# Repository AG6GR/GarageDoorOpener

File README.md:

# Garage Door Opener

<center></center>

A bare-bones ESP32 based HomeKit enabled garage door opener using [HomeSpan](https://github.com/HomeSpan/HomeSpan).

# Hardware

To avoid any modification to the garage door opener itself, I designed the board to use its own position sensor and emulate a wall switch to trigger the garage door movement. Some commercial products emulate a wireless remote and indeed the ESP32 does have some [special function hardware](https://github.com/HomeSpan/HomeSpan/blob/master/docs/RMT.md) for generating pulse code signals, however I decided to skip the complexity for this first revision as the holiday season presented some serious schedule pressure for getting this finished. Likewise, for the door position sensor some products use a tilt sensor with the assumption the board would be glued to the moving door itself. I again opted for the simpler solution of a microswitch mounted on one of the door's guide rails to avoid the complexity of dealing with battery power and wireless control.

<center></center>

To actuate the door, a wall switch normally would short a pair of lines connected to terminals on the back of the garage door opener. I measured these terminals with a voltmeter and found the high side was pulled up to 24V nominal, above some floating ground potential. Also of note is that the threshold voltage for triggering was quite low, less than 0.1V difference. The ideal part to use in this case would be a small relay, but I didn't have any on hand. As an alternative, I ended up using an optoisolator with an NPN transistor in a Darlington configuration to achieve the isolation and current capacity needed to drive the opener's trigger line low.

One unexpected issue that came up after the board arrived was that the NPN BJT was not fully turning on before the line voltage collapsed, leaving the line stuck at a ~0.7V base emitter diode voltage, which was just a bit above the threshold voltage for triggering the opener. I bodged in a 0.1 µF capacitor between the high/low side of the screw terminal to fix this. The extra capacitance ensures the BJT has just enough time to fully turn on, driving the line completely low and triggering the opener.

# Firmware

The firmware relies on the excellent [HomeSpan](https://github.com/HomeSpan/HomeSpan) project to implement HomeKit support. It was very straightforward to implement a GarageDoorOpener service and hook it up to the appropriate inputs/outputs. With some fine tuning of switch debouncing, everything was installed and ready by Christmas.

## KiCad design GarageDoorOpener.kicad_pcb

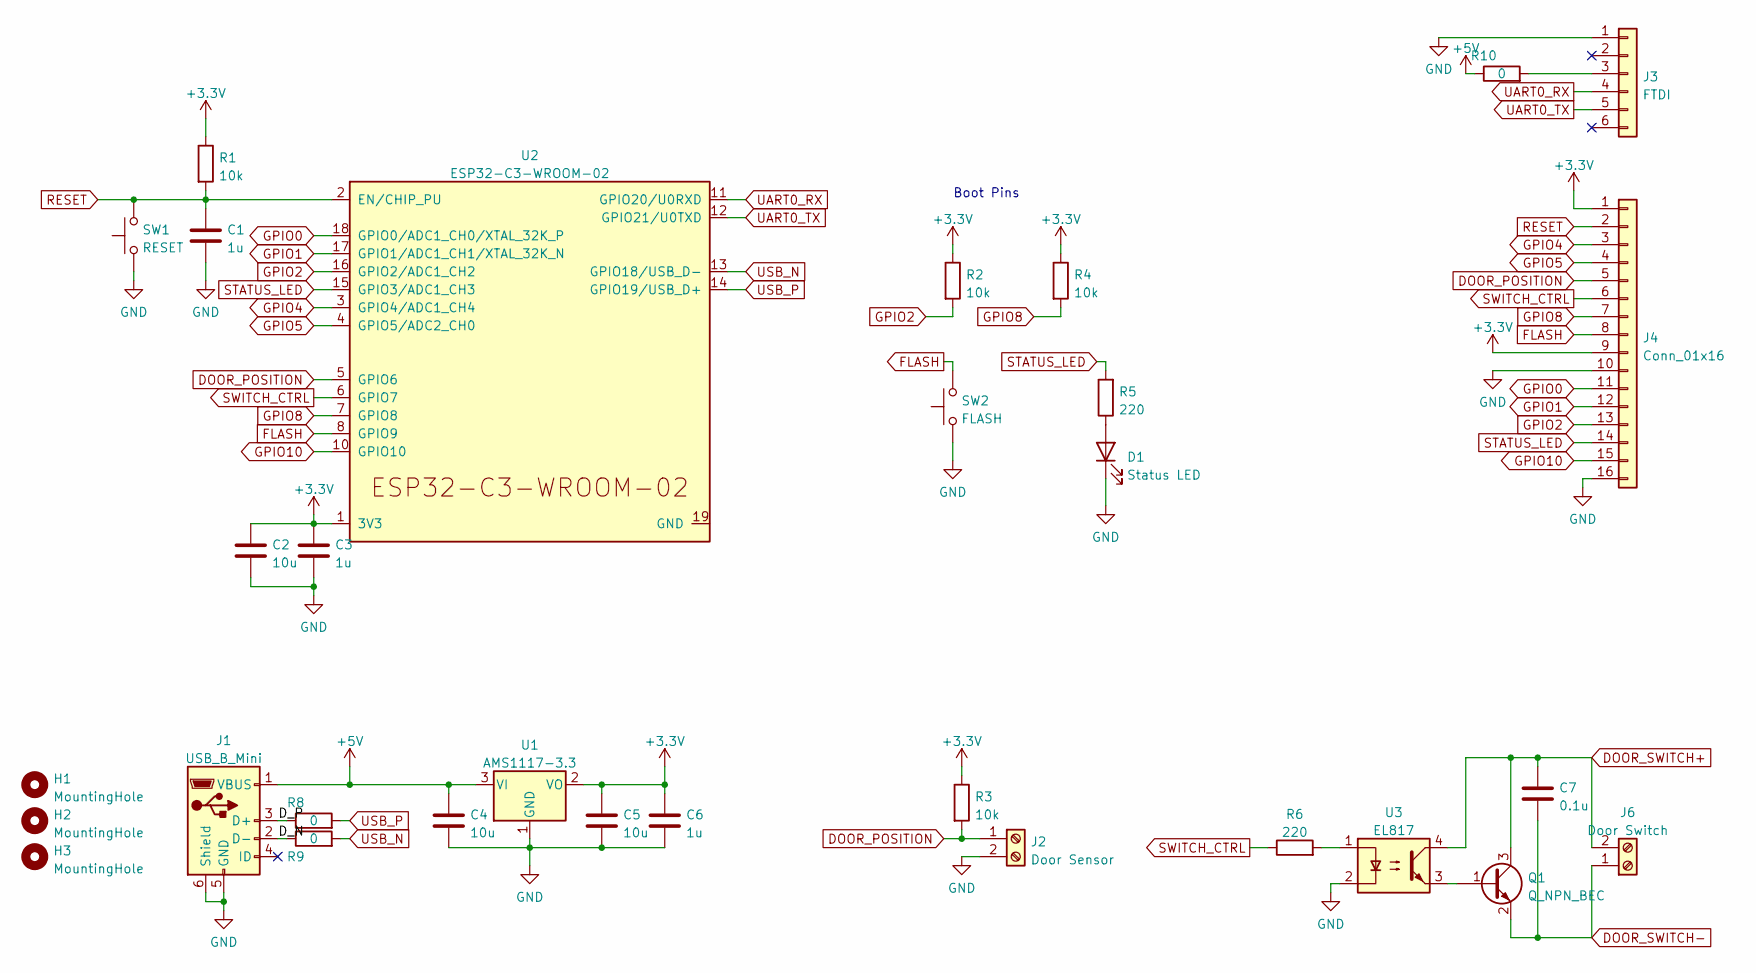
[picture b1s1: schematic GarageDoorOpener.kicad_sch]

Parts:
C1, C3, C6: 1u; C_0805_2012Metric
C2, C4, C5: 10u; C_0805_2012Metric
C7: 0.1u; C_0805_2012Metric
D1: Status LED; LED_0603_1608Metric
H1, H2, H3: MountingHole; MountingHole_3.2mm_M3
J1: USB_B_Mini; USB_Mini-B_Lumberg_2486_01_Horizontal
J2: Door Sensor; TerminalBlock_bornier-2_P5.08mm
J3: FTDI; PinHeader_1x06_P2.54mm_Vertical
J4: Conn_01x16; PinHeader_1x16_P2.54mm_Vertical
J6: Door Switch; TerminalBlock_bornier-2_P5.08mm
Q1: Q_NPN_BEC; SOT-23
R1, R2, R3, R4: 10k; R_0603_1608Metric
R5, R6: 220; R_0603_1608Metric
R8, R9, R10: 0; R_0603_1608Metric
SW1: RESET; SW_SPST_TL3342
SW2: FLASH; SW_SPST_TL3342
U1: AMS1117-3.3; SOT-223-3_TabPin2
U2: ESP32-C3-WROOM-02
U3: EL817; EL3H7

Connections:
+3.3V: C2.1, C3.1, C5.1, C6.1, J4.1, J4.9, R1.1, R2.1, R3.1, R4.1, U1.2 (VO), U2.1 (3V3)
+5V: C4.1, J1.1 (VBUS), R10.1, U1.3 (VI)
/D_N: J1.2 (D-), R9.1
/D_P: J1.3 (D+), R8.1
DOOR_POSITION: J2.1, J4.5, R3.2, U2.5 (GPIO6)
DOOR_SWITCH+: C7.1, J6.2, Q1.3 (C), U3.4
DOOR_SWITCH-: C7.2, J6.1, Q1.2 (E)
FLASH: J4.8, SW2.2, U2.8 (GPIO9)
GPIO0: J4.11, U2.18 (GPIO0/ADC1_CH0/XTAL_32K_P)
GPIO1: J4.12, U2.17 (GPIO1/ADC1_CH1/XTAL_32K_N)
GPIO2: J4.13, R2.2, U2.16 (GPIO2/ADC1_CH2)
GPIO4: J4.3, U2.3 (GPIO4/ADC1_CH4)
GPIO5: J4.4, U2.4 (GPIO5/ADC2_CH0)
GPIO8: J4.7, R4.2, U2.7 (GPIO8)
GPIO10: J4.15, U2.10 (GPIO10)
unnamed: D1.2 (A), R5.1
unnamed: J3.3, R10.2
unnamed: Q1.1 (B), U3.3
unnamed: R6.2, U3.1
RESET: C1.1, J4.2, R1.2, SW1.2, U2.2 (EN/CHIP_PU)
STATUS_LED: J4.14, R5.2, U2.15 (GPIO3/ADC1_CH3)
SWITCH_CTRL: J4.6, R6.1, U2.6 (GPIO7)
UART0_RX: J3.4, U2.11 (GPIO20/U0RXD)
UART0_TX: J3.5, U2.12 (GPIO21/U0TXD)
USB_N: R9.2, U2.13 (GPIO18/USB_D-)
USB_P: R8.2, U2.14 (GPIO19/USB_D+)

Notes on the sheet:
Boot Pins

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
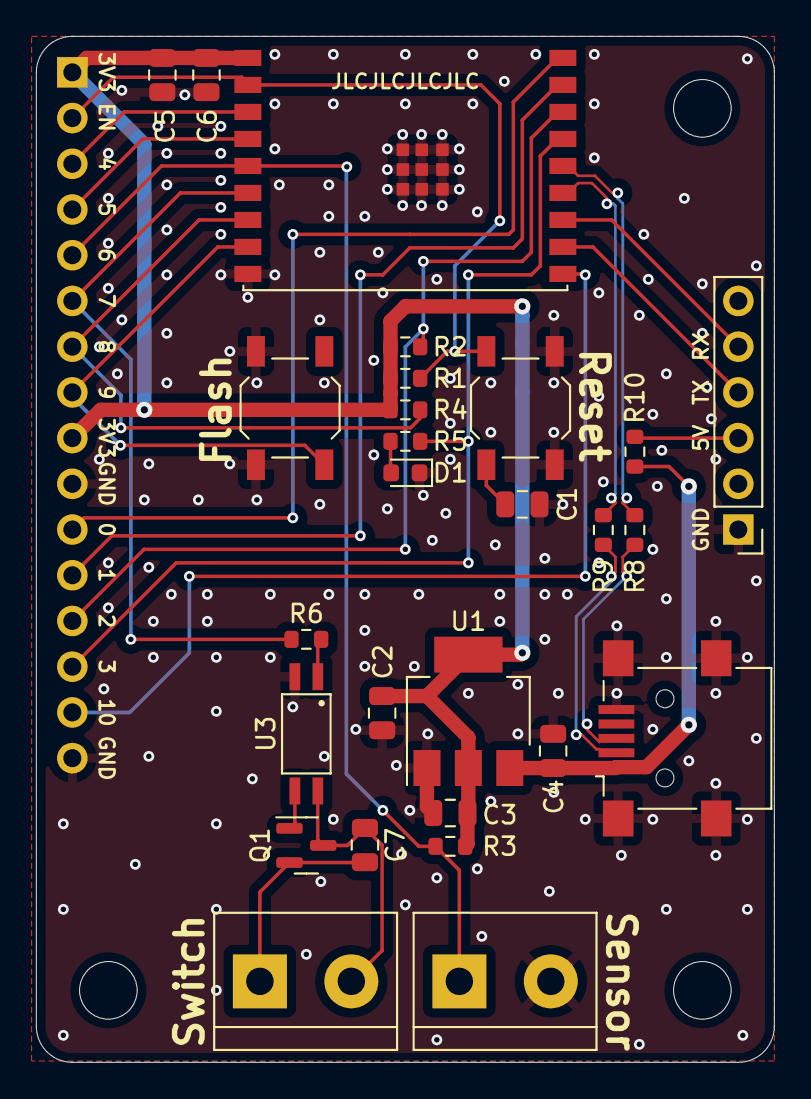
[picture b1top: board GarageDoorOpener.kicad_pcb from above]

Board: 2 copper layers, 41.0 x 57.0 mm, 31 parts (0 on the bottom side), 27 nets.

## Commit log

2022-12-14 Board rev 1.0
2022-12-15 Firmware mock up
2022-12-15 Add schematic
2022-12-15 Rename to GarageDoor
2022-12-15 Add status LED pin
2022-12-19 Firmware first rev
2022-12-19 Remove LED test
2022-12-19 Enable weblog
2022-12-19 Improve handling of external triggers and switch debouncing
2023-01-02 Update copyright
2023-01-02 Add README
2023-01-02 Board rev 1.1, add switch capacitor
2023-01-02 Add images
